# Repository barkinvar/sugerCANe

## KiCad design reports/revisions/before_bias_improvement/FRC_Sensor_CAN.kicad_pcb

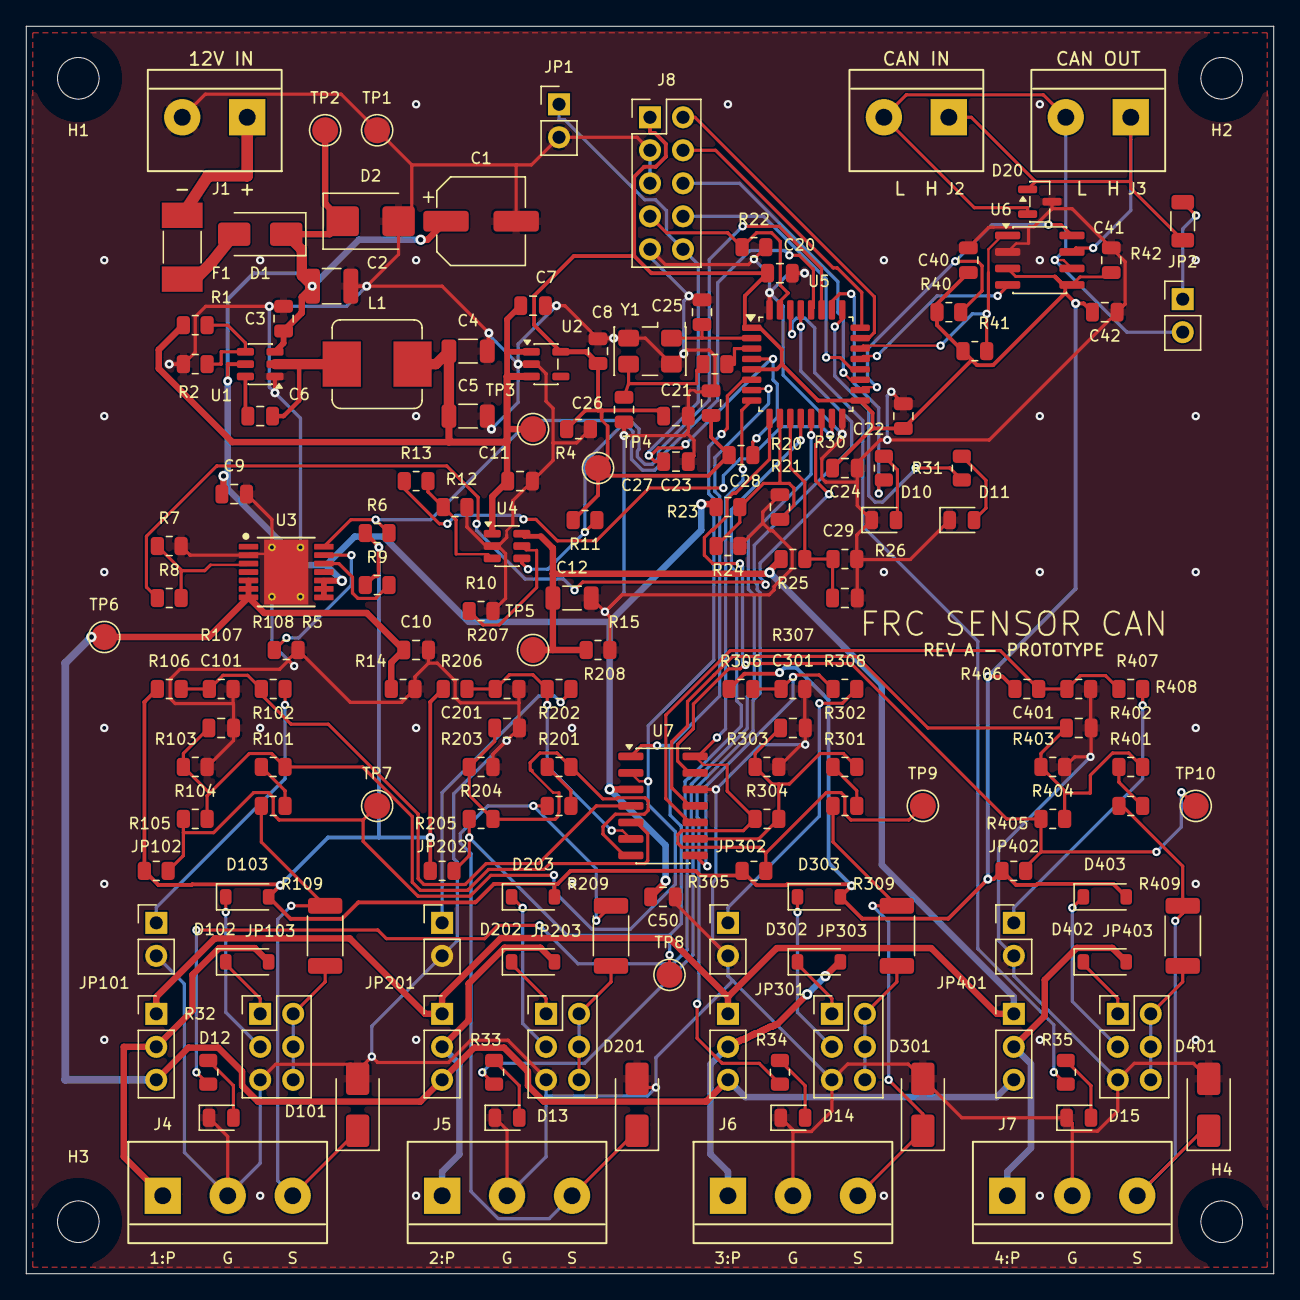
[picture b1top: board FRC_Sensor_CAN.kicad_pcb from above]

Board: 2 copper layers, 96.0 x 96.0 mm, 163 parts (0 on the bottom side), 89 nets.

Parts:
C1: 47uF; CP_Elec_6.3x7.7
C2: 10uF; C_1210_3225Metric
C3, C6, C9, C11, C20, C21, C22, C27, C40, C41, C50: 100nF; C_0805_2012Metric
C4, C5: 22uF; C_1206_3216Metric
C7, C10, C23, C42: 1uF; C_0805_2012Metric
C8, C24: 4.7uF; C_0805_2012Metric
C12: 10uF; C_1206_3216Metric
C25, C26: 30pF; C_0805_2012Metric
C28, C29: 10nF; C_0805_2012Metric
C101, C201, C301, C401: 1nF; C_0805_2012Metric
D1: SS36; D_SMA
D2: SMBJ18A; D_SMB
D10, D12, D13, D14, D15: GREEN; LED_0805_2012Metric
D11: RED; LED_0805_2012Metric
D20: ESD2CAN24-Q1; SOT-23
D101, D201, D301, D401: SMAJ30A; D_SMA
D102, D103, D202, D203, D302, D303, D402, D403: BAT46W; D_SOD-123
F1: 1.5A FAST; Fuse_Littelfuse-NANO2-451_453
H1, H2, H3, H4: M3 NPTH
J1, J2, J3: 2P 5.00mm; Wuerth_691137710002
J4, J5, J6, J7: 3P 5.00mm; Wuerth_691137710003
J8: DEBUG; PinHeader_2x05_P2.54mm_Vertical
JP1, JP2, JP102, JP202, JP302, JP402: SELECT; PinHeader_1x02_P2.54mm_Vertical
JP101, JP201, JP301, JP401: SELECT; PinHeader_1x03_P2.54mm_Vertical
JP103, JP203, JP303, JP403: SELECT; PinHeader_2x03_P2.54mm_Vertical
L1: 10uH; L_Bourns_SRP7028A_7.3x6.6mm
R1, R7, R12, R14, R23, R106, R206, R306, R406: 100k; R_0805_2012Metric
R2: 13.7k; R_0805_2012Metric
R4, R6, R9, R11, R15, R21, R22, R24, R25, R26, R40, R41, R105, R205, R305, R405: 10k; R_0805_2012Metric
R5: 4.87k; R_0805_2012Metric
R8: 4.7k; R_0805_2012Metric
R10: 59k; R_0805_2012Metric
R13, R30, R31, R32, R33, R34, R35: 1k; R_0805_2012Metric
R20: 0; R_0805_2012Metric
R42: 120; R_1206_3216Metric
R101, R102, R201, R202, R301, R302, R401, R402: 110k; R_0805_2012Metric
R103, R203, R303, R403: 20k; R_0805_2012Metric
R104, R204, R304, R404: 910k; R_0805_2012Metric
R107, R207, R307, R407: 17.8k; R_0805_2012Metric
R108, R208, R308, R408: 7.15k; R_0805_2012Metric
R109, R209, R309, R409: 4.7k; R_2010_5025Metric
TP1: GND; TestPoint_Pad_D2.0mm
TP2: VIN_PROT; TestPoint_Pad_D2.0mm
TP3: V5_INTERNAL; TestPoint_Pad_D2.0mm
TP4: +3V3; TestPoint_Pad_D2.0mm
TP5: SENSOR_5V; TestPoint_Pad_D2.0mm
TP6: SENSOR_VBAT; TestPoint_Pad_D2.0mm
TP7: INPUT1; TestPoint_Pad_D2.0mm
TP8: INPUT2; TestPoint_Pad_D2.0mm
TP9: INPUT3; TestPoint_Pad_D2.0mm
TP10: INPUT4; TestPoint_Pad_D2.0mm
U1: LMR51420XDDCR; TSOT-23-6
U2: AP2112K-3.3; SOT-23-5
U3: TPS1H100A-Q1; TI_PWP0014K_HTSSOP14_EP
U4: TPS2553DBVR-1; SOT-23-6
U5: STM32F042K6T6; LQFP-32_7x7mm_P0.8mm
U6: TCAN3413DR; SOIC-8_3.9x4.9mm_P1.27mm
U7: LM2901BIDR; SOIC-14_3.9x8.7mm_P1.27mm
Y1: 8MHz 18pF; Crystal_SMD_5032-4Pin_5.0x3.2mm

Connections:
+3V3: C8.1, C20.1, C21.1, C22.1, C23.1, C24.1, C40.1, C41.1, C42.1, D103.2, D203.2, D303.2, D403.2, J8.1, R4.1, R6.1, R9.1, R11.1, R21.1, R40.1, R41.1, R105.1, R106.1, R205.1, R206.1, R305.1, R306.1, R405.1, R406.1, TP4.1, U2.5, U5.1, U5.5, U5.17, U6.3, U6.5
ADC_5V: C29.1, R25.2, R26.1, U5.11
ADC_VBAT: C28.1, R23.2, R24.1, U5.10
BIAS1: JP103.2, JP103.4, JP103.6, R109.1
BIAS2: JP203.2, JP203.4, JP203.6, R209.1
BIAS3: JP303.2, JP303.4, JP303.6, R309.1
BIAS4: JP403.2, JP403.4, JP403.6, R409.1
BIAS_3V3_1: D103.1, JP103.3
BIAS_3V3_2: D203.1, JP203.3
BIAS_3V3_3: D303.1, JP303.3
BIAS_3V3_4: D403.1, JP403.3
BIAS_PORT1: D102.1, JP103.1
BIAS_PORT2: D202.1, JP203.1
BIAS_PORT3: D302.1, JP303.1
BIAS_PORT4: D402.1, JP403.1
BOOT0: J8.7, R22.1, U5.31
BUCK_CB: C6.1, U1.6
BUCK_FB: R1.2, R2.1, U1.4
BUCK_SW: C6.2, L1.1, U1.2
CANH: D20.1, J2.1, J3.1, R42.1, U6.7
CANL: D20.2, J2.2, J3.2, JP2.2, U6.6
CAN_RX: U5.21, U6.4
CAN_STB: R40.2, U5.18, U6.8
CAN_TERM: JP2.1, R42.2
CAN_TX: R41.2, U5.22, U6.1
GND: C1.2, C2.2, C3.2, C4.2, C5.2, C7.2, C8.2, C9.2, C10.2, C11.2, C12.2, C20.2, C21.2, C22.2, C23.2, C24.2, C25.2, C26.2, C27.2, C28.2, C29.2, C40.2, C41.2, C42.2, C50.2, C101.2, C201.2, C301.2, C401.2, D2.2, D10.1, D11.1, D12.1, D13.1, D14.1, D15.1, D20.3, D101.2, D201.2, D301.2, D401.2, J1.2, J4.2, J5.2, J6.2, J7.2, J8.3, J8.5, J8.9, JP1.2, JP102.2, JP103.5, JP202.2, JP203.5, JP302.2, JP303.5, JP402.2, JP403.5, R2.2, R4.2, R5.2, R7.2, R10.2, R12.2, R14.2, R15.2, R22.2, R24.2, R26.2, R103.2, R107.2, R203.2, R207.2, R303.2, R307.2, R403.2, R407.2, TP1.1, U1.1, U2.2, U3.2, U3.15, U4.2, U5.16, U5.32, U6.2, U7.12, Y1.2, Y1.4
HSE_IN: C25.1, U5.2, Y1.1
HSE_OUT: R20.1, U5.3
HSE_XTAL_OUT: C26.1, R20.2, Y1.3
INPUT1: R104.1, R105.2, TP7.1, U5.6, U7.2
INPUT2: R204.1, R205.2, TP8.1, U5.7, U7.1
INPUT3: R304.1, R305.2, TP9.1, U5.8, U7.14
INPUT4: R404.1, R405.2, TP10.1, U5.9, U7.13
LED1: R32.1, U5.12
LED1_A: D12.2, R32.2
LED2: R33.1, U5.13
LED2_A: D13.2, R33.2
LED3: R34.1, U5.29
LED3_A: D14.2, R34.2
LED4: R35.1, U5.30
LED4_A: D15.2, R35.2
LOW_SEL1: JP102.1, R108.2
LOW_SEL2: JP202.1, R208.2
LOW_SEL3: JP302.1, R308.2
LOW_SEL4: JP402.1, R408.2
NRST: C27.1, J8.10, JP1.1, R21.2, U5.4
REF1: R106.2, R107.1, R108.1, U7.4
REF2: R206.2, R207.1, R208.1, U7.6
REF3: R306.2, R307.1, R308.1, U7.8
REF4: R406.2, R407.1, R408.1, U7.10
SENSE1: C101.1, R102.2, R103.1, R104.2, U7.5
SENSE2: C201.1, R202.2, R203.1, R204.2, U7.7
SENSE3: C301.1, R302.2, R303.1, R304.2, U7.9
SENSE4: C401.1, R402.2, R403.1, R404.2, U7.11
SENSOR_5V: C12.1, JP101.1, JP201.1, JP301.1, JP401.1, R15.1, R25.1, TP5.1, U4.6
SENSOR_VBAT: C10.1, JP101.3, JP201.3, JP301.3, JP401.3, R14.1, TP6.1, U3.5, U3.6, U3.7
SIG1: D101.1, J4.3, R101.1, R109.2
SIG2: D201.1, J5.3, R201.1, R209.2
SIG3: D301.1, J6.3, R301.1, R309.2
SIG4: D401.1, J7.3, R401.1, R409.2
SIG_MID1: R101.2, R102.1
SIG_MID2: R201.2, R202.1
SIG_MID3: R301.2, R302.1
SIG_MID4: R401.2, R402.1
STATUS_GREEN: R30.1, U5.26
STATUS_GREEN_A: D10.2, R30.2
STATUS_RED: R31.1, U5.25
STATUS_RED_A: D11.2, R31.2
SWCLK: J8.4, U5.24
SWDIO: J8.2, U5.23
UART_RX: J8.8, U5.20
UART_TX: J8.6, U5.19
V5_ENABLE: R13.1, U5.15
V5_EN_PIN: R12.1, R13.2, U4.3
V5_FAULT_N: R11.2, U4.4, U5.28
V5_ILIM: R10.1, U4.5
V5_INTERNAL: C4.1, C5.1, C7.1, C11.1, L1.2, R1.1, TP3.1, U2.1, U2.3, U4.1
VBAT_DIAG_EN: R9.2, U3.12
VBAT_ENABLE: R8.1, U5.14
VBAT_EN_PIN: R7.1, R8.2, U3.3
VBAT_FAULT_N: R6.2, U3.14, U5.27
VBAT_ILIM: R5.1, U3.13
VIN_FUSED: D1.2, F1.2
VIN_PROT: C1.1, C2.1, C3.1, C9.1, C50.1, D1.1, D2.1, R23.1, TP2.1, U1.3, U1.5, U3.8, U3.9, U3.10, U7.3
VIN_RAW: F1.1, J1.1
VPORT1: D102.2, J4.1, JP101.2
VPORT2: D202.2, J5.1, JP201.2
VPORT3: D302.2, J6.1, JP301.2
VPORT4: D402.2, J7.1, JP401.2

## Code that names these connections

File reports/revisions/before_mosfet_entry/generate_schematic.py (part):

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 (6,'PA0/IN1','input'),(7,'PA1/IN2','input'),(8,'PA2/IN3','input'),(9,'PA3/IN4','input'),
 (10,'PA4/ADC4','input'),(11,'PA5/ADC5','input'),(27,'PB4/BAT_FLT','input'),(28,'PB5/5V_FLT','input'),
 (31,'PB8/BOOT0','input'),(23,'PA13/SWDIO','bidirectional'),(24,'PA14/SWCLK','input')],
 [(21,'PA11/CAN_RX','input'),(22,'PA12/CAN_TX','output'),(18,'PA8/CAN_STB','output'),
 (19,'PA9/UART_TX','output'),(20,'PA10/UART_RX','input'),(14,'PB0/BAT_EN','output'),(15,'PB1/5V_EN','output'),
 (12,'PA6/LED1','output'),(13,'PA7/LED2','output'),(29,'PB6/LED3','output'),(30,'PB7/LED4','output'),
 (25,'PA15/RED','output'),(26,'PB3/GREEN','output')],
 top=[(1,'VDD','power_in'),(5,'VDDA','power_in'),(17,'VDDIO2','power_in')],
 bottom=[(16,'VSS','power_in'),(32,'VSS','power_in')],width=45.72)
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p.text('PROTECTED BATTERY ENTRY',15,28,1.8)
gp(p,'J1',14,24,labels=True)
f=gp(p,'F1',34,22);d=gp(p,'D1',49,22)
p.label('VIN_RAW',f['1']);path(p,f['2'],d['2']);p.label('VIN_FUSED',d['2'])
entry_y=d['1'][1];nodes=[]
for ref,gx,ang in [('D2',66,90),('C1',86,270),('C2',109,270),('C3',130,270)]:
    pins=gp(p,ref,gx,32,ang);node=(pins['1'][0],entry_y);nodes.append(node)
    p.wire(node,pins['1']);p.junction(node);p.label('GND',pins['2'])
path(p,d['1'],*nodes);p.label('VIN_PROT',nodes[-1],180)
for i in range(1,7):gp(p,f'TP{i}',20+(i-1)*25,45,labels=True)
p.text('500 kHz BUCK / 5 V INTERNAL',15,130,1.8)
u=gp(p,'U1',40,66);l=gp(p,'L1',74,66);cb=gp(p,'C6',60,55)
vinx=18*2.54
path(p,u['3'],(vinx,u['3'][1]),(vinx,u['5'][1]),u['5']);p.label('VIN_PROT',(vinx,u['3'][1]))
p.label('GND',u['1'])
sw=(68*2.54,u['2'][1]);path(p,u['2'],sw,l['1']);p.label('BUCK_SW',sw)
path(p,u['6'],(50*2.54,u['6'][1]),(50*2.54,cb['1'][1]),cb['1']);p.label('BUCK_CB',cb['1'])
path(p,cb['2'],(sw[0],cb['2'][1]),sw);p.junction(sw)
c4=gp(p,'C4',86,77,270);c5=gp(p,'C5',103,77,270);c13=gp(p,'C13',119,77,270)
r1=gp(p,'R1',135,77,270);r2=gp(p,'R2',135,94,270)
rail=[l['2']]+[(pin['1'][0],l['2'][1]) for pin in [c4,c5,c13,r1]]
path(p,*rail);p.label('V5_INTERNAL',rail[-1],180)
for pin in [c4,c5,c13,r1]:
    node=(pin['1'][0],l['2'][1]);p.wire(node,pin['1']);p.junction(node)
for pin in [c4,c5,c13]:p.label('GND',pin['2'])
mid=(r1['2'][0],86*2.54)
path(p,r1['2'],mid,r2['1']);p.junction(mid);p.label('GND',r2['2'])
path(p,u['4'],(54*2.54,u['4'][1]),(54*2.54,mid[1]),mid);p.label('BUCK_FB',(54*2.54,mid[1]))
p.text('3.3 V LOGIC SUPPLY',15,245,1.8)
u=gp(p,'U2',42,106);c7=gp(p,'C7',20,104,270);c8=gp(p,'C8',67,104,270);r4=gp(p,'R4',88,104,270)
# Local labels keep the enable tie and the compact LDO drawing unambiguous.
for n in ['1','3']:p.label('V5_INTERNAL',u[n])
p.label('GND',u['2']);p.label('+3V3',u['5'],180)
for c,net in [(c7,'V5_INTERNAL'),(c8,'+3V3'),(r4,'+3V3')]:p.label(net,c['1']);p.label('GND',c['2'])
p.flag('GND',375.92,195.58);p.flag('VIN_PROT',375.92,215.9);p.flag('V5_INTERNAL',375.92,236.22)
p.text('6-18 V input target; protected distribution feed.\nVBAT output follows the protected entry voltage.\n5 V sensor output has a separate limit switch.\nR1/R2: 0.1%, 25 ppm/C.\nTP1:GND, 2:VIN, 3:5V, 4:3V3, 5:S5V, 6:SBAT.',243,261,1.0)

p=pages['sensor_power']
p.text('PROTECTED BATTERY PASSTHROUGH',15,30,1.8)
u=gp(p,'U3',52,31)
outx=70*2.54;p.label('VIN_PROT',u['8']);p.wire(u['7'],(outx,u['7'][1]))
for n in ['6','9']:p.wire(u[n],(u[n][0],43*2.54))
path(p,(u['6'][0],43*2.54),(u['9'][0],43*2.54));p.label('GND',(u['6'][0],43*2.54))
r=gp(p,'R8',25,30.5);down=gp(p,'R7',35,42,270)
p.label('VBAT_ENABLE',r['1']);path(p,r['2'],u['1'])
node=(down['1'][0],u['1'][1]);p.wire(node,down['1']);p.junction(node);p.label('VBAT_EN_PIN',r['2'],180);p.label('GND',down['2'])
for n in ['2','4']:p.label(PARTS['U3']['pins'][n],u[n])
c=gp(p,'C14',75,55,270)
path(p,u['5'],(65*2.54,u['5'][1]),(65*2.54,c['1'][1]),c['1']);p.label('VBAT_DELAY',c['1']);p.label('GND',c['2'])
r=gp(p,'R5',56,53,270);p.label('VBAT_ILIM',r['1']);p.label('GND',r['2'])
r=gp(p,'R9',25,54);p.label('+3V3',r['1']);p.label('VBAT_DIAG_EN',r['2'],180)
c=gp(p,'C9',22,20,270);p.label('VIN_PROT',c['1']);p.label('GND',c['2'])
c=gp(p,'C10',91,36,270);r=gp(p,'R14',114,36,270)
rail_y=u['7'][1];nodes=[(outx,rail_y),(c['1'][0],rail_y),(r['1'][0],rail_y)];path(p,*nodes)
for pin in [c,r]:p.wire((pin['1'][0],rail_y),pin['1']);p.label('GND',pin['2'])
p.label('SENSOR_VBAT',nodes[-1],180)
pull=gp(p,'R6',140,36,270);p.label('+3V3',pull['1'])
fy=47*2.54
path(p,u['3'],(77*2.54,u['3'][1]),(77*2.54,fy),(pull['2'][0],fy),pull['2']);p.label('VBAT_FAULT_N',(pull['2'][0],fy),180)

p.text('REGULATED 5 V SENSOR OUTPUT',15,168,1.8)
u=gp(p,'U4',52,81);p.label('V5_INTERNAL',u['1']);p.label('V5_ILIM',u['5']);p.label('GND',u['2'])
r=gp(p,'R13',25,81);down=gp(p,'R12',35,94,270)
p.label('V5_ENABLE',r['1']);path(p,r['2'],u['3'])
node=(down['1'][0],u['3'][1]);p.wire(node,down['1']);p.junction(node);p.label('V5_EN_PIN',r['2'],180);p.label('GND',down['2'])
r=gp(p,'R10',56,103,270);p.label('V5_ILIM',r['1']);p.label('GND',r['2'])
c=gp(p,'C11',22,73,270);p.label('V5_INTERNAL',c['1']);p.label('GND',c['2'])
c=gp(p,'C12',91,87,270);r=gp(p,'R15',114,87,270)
rail_y=u['6'][1];nodes=[u['6'],(c['1'][0],rail_y),(r['1'][0],rail_y)];path(p,*nodes)
for pin in [c,r]:p.wire((pin['1'][0],rail_y),pin['1']);p.label('GND',pin['2'])
p.label('SENSOR_5V',nodes[-1],180)
pull=gp(p,'R11',140,87,270);p.label('+3V3',pull['1']);fy=97*2.54
path(p,u['4'],(77*2.54,u['4'][1]),(77*2.54,fy),(pull['2'][0],fy),pull['2']);p.label('V5_FAULT_N',(pull['2'][0],fy),180)
p.text('Usable targets: 300 mA total on each rail, shared across all ports.\nBoth enable pins have hardware pulldowns. Firmware latches overload faults.\nTPS2553 -1 is the latching version. Clear only after inspecting sensor wiring.',15,278,1.15)

p=pages['controller']
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y=gp(p,'Y1',99,23);r=gp(p,'R20',128,23,180)
c1=gp(p,'C25',88,37,270);c2=gp(p,'C26',116,37,270)
a=(c1['1'][0],y['1'][1]);z=(c2['1'][0],y['3'][1])
path(p,a,y['1']);p.label('HSE_IN',a);p.wire(a,c1['1'])
path(p,y['3'],z,r['2']);p.wire(z,c2['1']);p.junction(z);p.label('HSE_XTAL_OUT',z)
p.label('HSE_OUT',r['1'],180)
cy=30*2.54
path(p,y['2'],(y['2'][0],cy),(y['4'][0],cy),y['4']);p.label('GND',(y['2'][0],cy))
for c in [c1,c2]:p.label('GND',c['2'])
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path(p,u['3'],(u['3'][0],top_y),(u['5'][0],top_y),u['5']);p.label('+3V3',(u['3'][0],top_y))
j=gp(p,'J2',75,24.5);gp(p,'J3',121,24.5,labels=True)
for n,m in [('7','1'),('6','2')]:path(p,u[n],j[m])
p.label('CANH',j['1']);p.label('CANL',j['2'])
r=gp(p,'R42',54,37);jp=gp(p,'JP2',75,37)
a=(43*2.54,u['7'][1]);z=(46*2.54,u['6'][1])
path(p,a,(a[0],r['1'][1]),r['1']);p.junction(a)
path(p,r['2'],(65*2.54,r['2'][1]),(65*2.54,jp['1'][1]),jp['1']);p.label('CAN_TERM',r['2'],180)
path(p,z,(z[0],43*2.54),(69*2.54,43*2.54),(69*2.54,jp['2'][1]),jp['2']);p.junction(z)
gp(p,'D20',121,42,labels=True)
for ref,gx,net in [('R40',20,'CAN_STB'),('R41',48,'CAN_TX')]:
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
